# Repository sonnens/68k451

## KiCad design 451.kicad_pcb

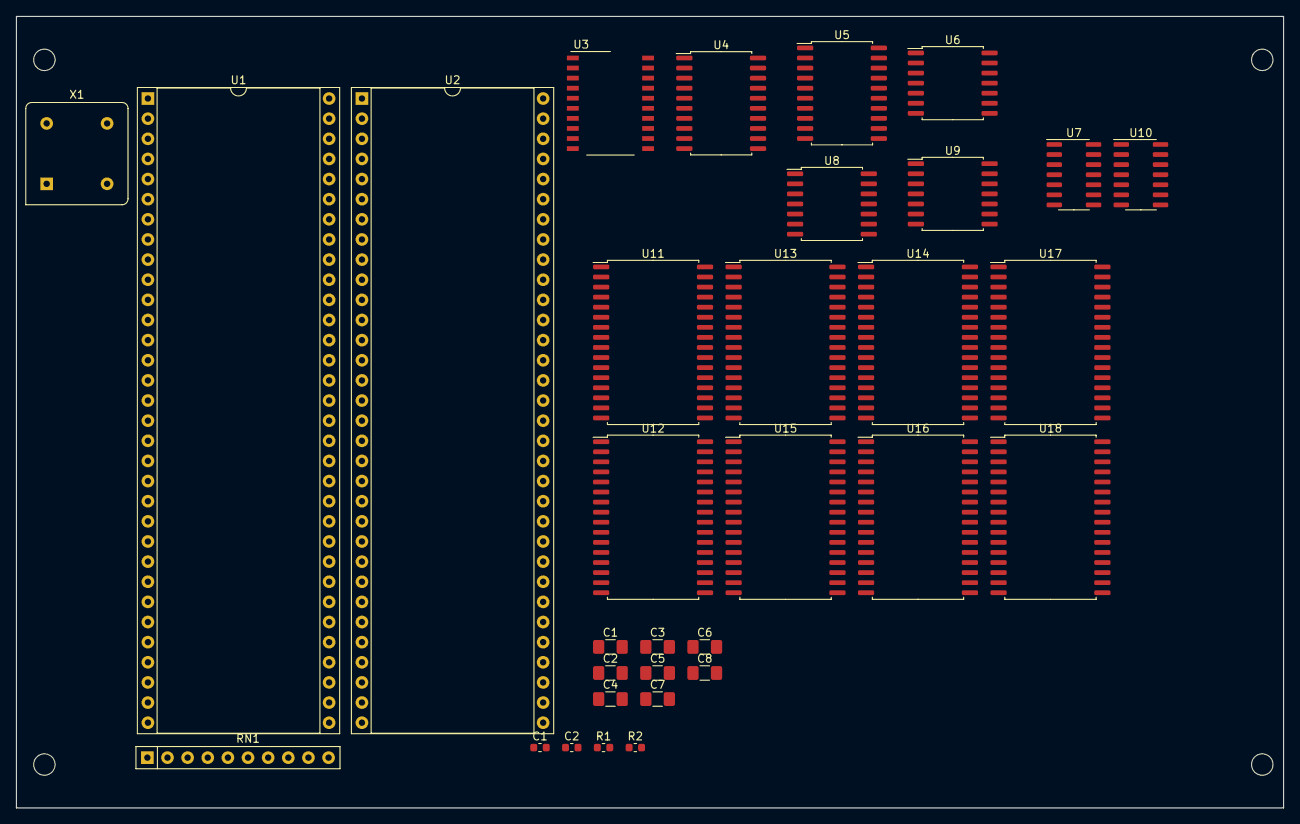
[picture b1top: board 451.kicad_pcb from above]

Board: 2 copper layers, 159.9 x 99.9 mm, 36 parts (0 on the bottom side), 68 nets, no tracks yet.

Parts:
C1, C2, C3, C4, C5, C6, C7, C8: C; C_1206_3216Metric_Pad1.42x1.75mm_HandSolder
C1#2, C2#2: C; C_0603_1608Metric
MK1, MK2, MK3, MK4: Mounting_Hole_PAD; MountingHole_2.7mm
R1, R2: 2.2k; R_0603_1608Metric
RN1: 47k; R_Array_SIP10
U1: 68010D; DIP-64_W22.86mm_Socket
U2: 68451; DIP-64_W22.86mm_Socket
U3: 74LS245; SO-20_12.8x7.5mm_P1.27mm
U4: 74LS245; SOIC-20W_7.5x12.8mm_P1.27mm
U5: 74LS04; SOIC-20W_7.5x12.8mm_P1.27mm
U6: 74LS00; SOIC-14W_7.5x9mm_P1.27mm
U7: 74LS08; SOIC-14_3.9x8.7mm_P1.27mm
U8: 74LS125; SOIC-14W_7.5x9mm_P1.27mm
U9: 74LS32; SOIC-14W_7.5x9mm_P1.27mm
U10: 74LS05; SOIC-14_3.9x8.7mm_P1.27mm
U11, U12, U13, U14, U15, U16, U17, U18: IS61C5128AS-25QLI; SSOP-32_11.305x20.495mm_P1.27mm
X1: 8Mhz; Oscillator_DIP-8

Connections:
+5V: C1.1, C2.1, C3.1, C4.1, C5.1, C6.1, C7.1, C8.1, R1.1, R2.1, RN1.1, U1.14, U1.49, U2.25, U2.56, U3.20, U4.20, U5.14, U6.14, U8.14, U9.14, X1.8
/A8: U1.36, U2.32
/A9: U1.37, U2.33
/A10: U1.38, U2.34
/A11: U1.39, U2.35
/A12: U1.40, U2.36
/A13: U1.41, U2.37
/A14: U1.42, U2.38
/A15: U1.43, U2.39
/A16: U1.44, U2.40
/A17: U1.45, U2.42
/A18: U1.46, U2.43
/A19: U1.47, U2.44
/A20: U1.48, U2.45
/A21: U1.50, U2.46
/A22: U1.51, U2.47
/A23: U1.52, U2.48
/ANY: RN1.3, U2.20
/D0: U1.5, U3.2
/D1: U1.4, U3.3
/D2: U1.3, U3.4
/D3: U1.2, U3.5
/D4: U1.1, U3.6
/D5: U1.64, U3.7
/D6: U1.63, U3.8
/D7: U1.62, U3.9
/D8: U1.61, U4.2
/D9: U1.60, U4.3
/D10: U1.59, U4.4
/D11: U1.58, U4.5
/D12: U1.57, U4.6
/D13: U1.56, U4.7
/D14: U1.55, U4.8
/D15: U1.54, U4.9
/DTACK: RN1.2, U1.10, U2.15
/ED: RN1.6, U2.16, U3.19, U4.19
/GO: RN1.5, U2.19
/\AS: U5.4, U6.2
/\MAS: U5.2, U6.1
ALL: RN1.4, RN1.7, U2.21, U10.2
AS: U1.6, U2.13, U5.3, U5.9
CLK: U1.15, U2.24, X1.5
FC0: U1.28, U2.12, U7.1
FC1: U1.27, U2.11, U7.2
FC2: U1.26, U2.10, U7.4
GND: C1.2, C2.2, C3.2, C4.2, C5.2, C6.2, C7.2, C8.2, U1.16, U1.53, U2.4, U2.8, U2.9, U2.41, U3.10, U4.10, U5.7, U6.7, U8.4, U8.7, U8.13, U9.7, X1.4
LDS: U1.8, U9.10
MAS: RN1.8, U2.2, U5.1, U8.1, U8.10, U10.4
MLDS: U2.18, U8.11
MUDS: U2.17, U8.6
unnamed: U5.5, U9.3
unnamed: U5.6, U9.4
unnamed: U5.8, U7.5
unnamed: U7.3, U7.9
unnamed: U7.6, U7.10
unnamed: U8.2, U9.6
unnamed: U8.9, U9.8
unnamed: U7.8, U10.1, U10.3
PA1: U1.29, U2.27
PA2: U1.30, U2.28
PA3: U1.31, U2.29
PA4: U1.32, U2.30
PA5: U1.33, U2.31
PLDS: R2.2, RN1.10, U8.5, U8.8
PUDS: R1.2, RN1.9, U8.3, U8.12
RW: U1.9, U2.26, U3.1, U4.1, U9.1
UDS: U1.7, U9.5
WIN: U2.5, U9.2

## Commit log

2021-02-05 finish memory layout thing
